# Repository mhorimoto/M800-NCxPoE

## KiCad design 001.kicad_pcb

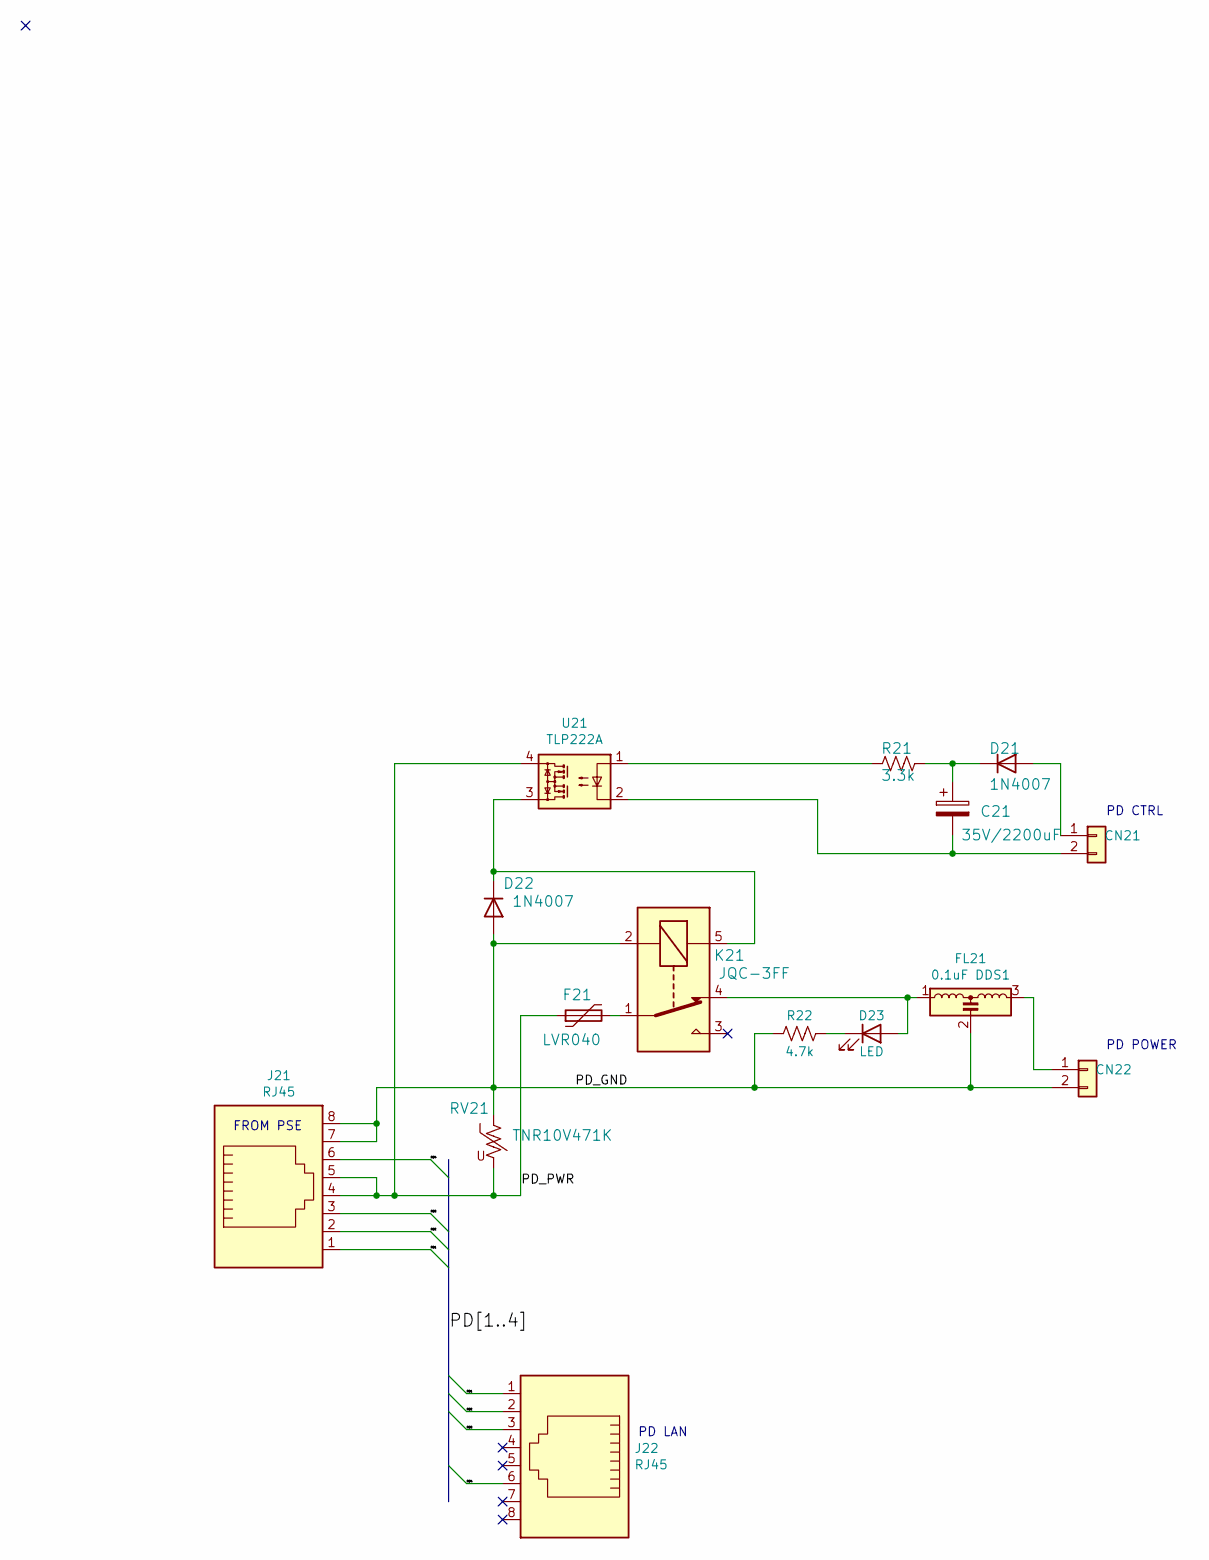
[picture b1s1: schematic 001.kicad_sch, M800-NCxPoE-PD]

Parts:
C21: 35V/2200uF; CP_Radial_D16.0mm_P7.50mm
CN21, CN22: 02-XH-A; JST_XH_B2B-XH-A_1x02_P2.50mm_Vertical
D21, D22: 1N4007; D_DO-41_SOD81_P10.16mm_Horizontal
D23: LED; LED_D3.0mm
F21: LVR040; Fuse_BelFuse_0ZRE0033FF_L11.4mm_W3.8mm
FL21: 0.1uF DDS1; DSS1
J21, J22: RJ45; RJ45_Neltron_7810-8P8C
K21: JQC-3FF; Relay_SPDT_Omron-G5LE-1
R21: 3.3k; R_Axial_DIN0207_L6.3mm_D2.5mm_P10.16mm_Horizontal
R22: 4.7k; R_Axial_DIN0207_L6.3mm_D2.5mm_P10.16mm_Horizontal
RV21: TNR10V471K; RV_Disc_D12mm_W3.9mm_P7.5mm
U21: TLP222A; DIP-4_W7.62mm

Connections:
/PD1: J21.1, J22.1
/PD2: J21.2, J22.2
/PD3: J21.3, J22.3
/PD4: J21.6, J22.6
/PD_GND: CN22.2, D22.2 (A), FL21.2, J21.7, J21.8, K21.2, R22.2, RV21.1
/PD_PWR: F21.1, J21.4, J21.5, RV21.2, U21.4
unnamed: C21.1, D21.1 (K), R21.1
unnamed: C21.2, CN21.2, U21.2
unnamed: CN21.1, D21.2 (A)
unnamed: CN22.1, FL21.3
unnamed: D22.1 (K), K21.5, U21.3
unnamed: D23.1 (K), R22.1
unnamed: D23.2 (A), FL21.1, K21.4
unnamed: F21.2, K21.1
unnamed: R21.2, U21.1

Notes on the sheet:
PD LAN
FROM PSE
PD CTRL
PD POWER

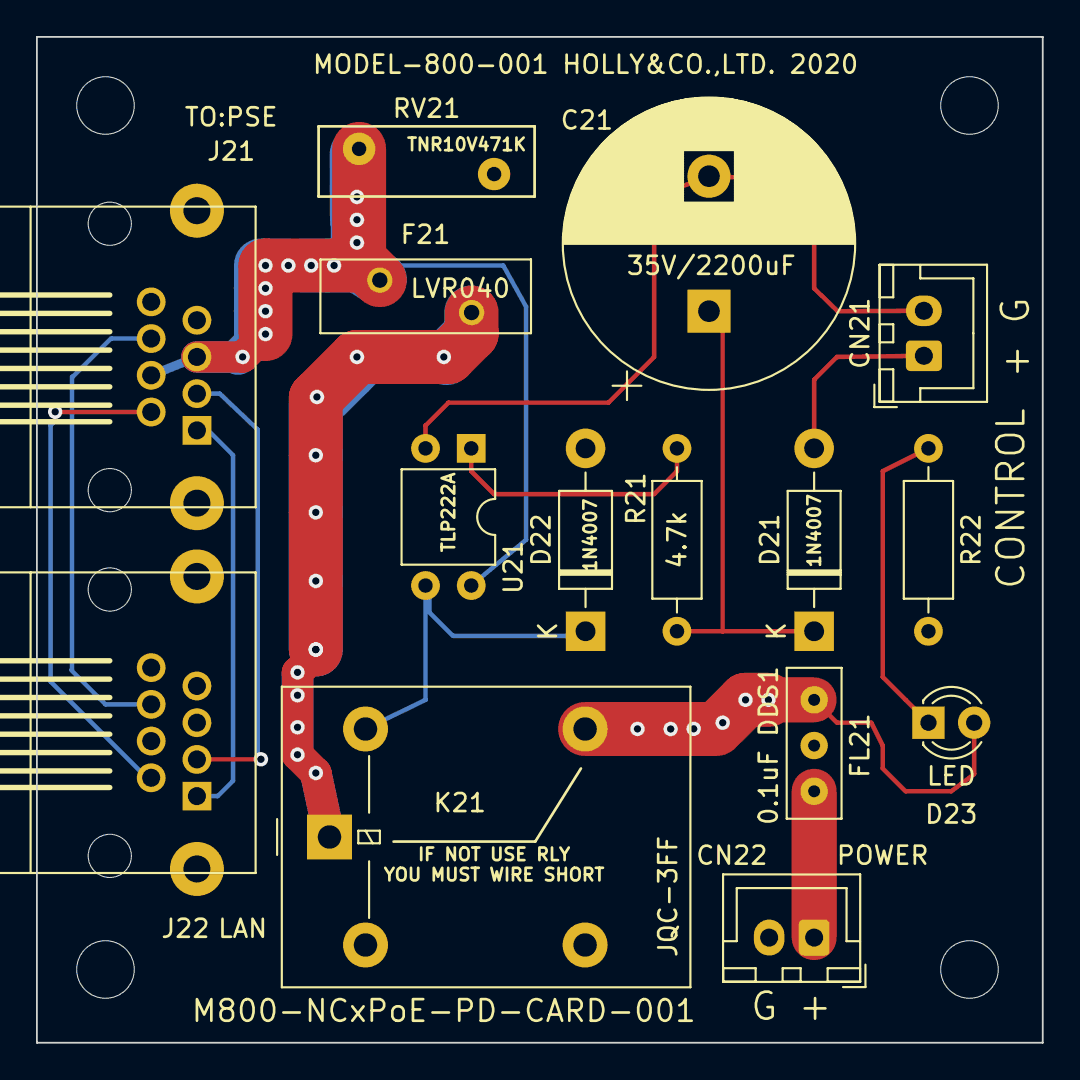
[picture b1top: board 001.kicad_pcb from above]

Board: 2 copper layers, 55.9 x 55.9 mm, 15 parts (0 on the bottom side), 15 nets.

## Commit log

2020-06-22 リレーコイル電源を5V化する必要が有る場合にはレギュレータを入れる
2020-06-23 実機試験用
2020-06-28 これからPCB
2020-06-30 PSE側art work
2020-07-01 PCB変更とRJ45コネクタのFP作り
2020-07-02 もうちょっとRJ45コネクタは大変更
2020-07-03 RJ45 SOCKETを組み直し
2020-07-06 更に小型化
2020-07-18 一応完成、これからガーバー
2020-07-24 PSEとPDを別図面にした
2020-08-05 テストプログラム追加
2024-02-10 version合わせ
2024-12-23 KiCAD Version
